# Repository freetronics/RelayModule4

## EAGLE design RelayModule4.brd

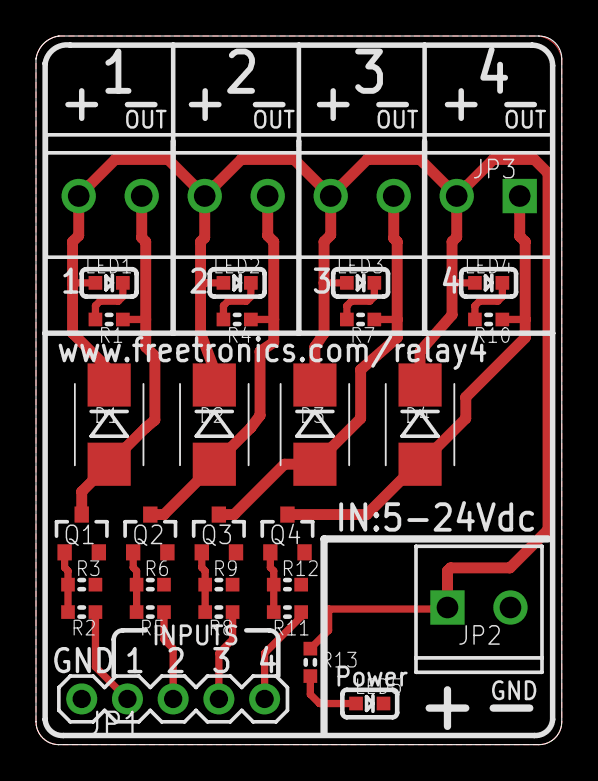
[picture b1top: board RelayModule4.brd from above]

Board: 2 copper layers, 29.2 x 39.4 mm, 30 parts (1 on the bottom side), 19 nets.

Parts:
D1, D2, D3, D4: 1N4004 SMB; SMB-DIODE
JP1: Power; 1X05
JP2: SCREWTERMINAL-3.5MM-2
JP3: TERMINALBLOCK_3.5MM_8
LED1: CH1/RED; LED-0603
LED2: CH2/RED; LED-0603
LED3: CH3/RED; LED-0603
LED4: CH4/RED; LED-0603
LED5: PWR/GRN; LED-0603
Q1, Q2, Q3, Q4: 2N7002; SOT23-3
R1, R2, R4, R5, R7, R8, R10, R11: 1K; 0603
R3, R6, R9, R12: 10K; 0603
R13: 2K2; 0603
U$5: OSHW_10X200_NOTEXT

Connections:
CH1: JP1.2, R2.2
CH2: JP1.3, R5.2
CH3: JP1.4, R8.2
CH4: JP1.5, R11.2
GND: JP1.1, JP2.2, LED5.C, Q1.2, Q2.2, Q3.2, Q4.2, R3.1, R6.1, R9.1, R12.1
unnamed: Q1.1, R2.1, R3.2
unnamed: D1.A, JP3.7, Q1.3, R1.2
unnamed: D2.A, JP3.5, Q2.3, R4.2
unnamed: LED5.A, R13.1
unnamed: Q2.1, R5.1, R6.2
unnamed: D3.A, JP3.3, Q3.3, R7.2
unnamed: Q3.1, R8.1, R9.2
unnamed: D4.A, JP3.1, Q4.3, R10.2
unnamed: Q4.1, R11.1, R12.2
unnamed: LED2.C, R4.1
unnamed: LED4.C, R10.1
unnamed: LED3.C, R7.1
unnamed: LED1.C, R1.1
V+: D1.C, D2.C, D3.C, D4.C, JP2.1, JP3.2, JP3.4, JP3.6, JP3.8, LED1.A, LED2.A, LED3.A, LED4.A, R13.2

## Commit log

2012-02-14 Initial project import
2012-02-14 Shuffling stuff around
2012-02-14 Rearranging and routing
2012-02-28 Layout and schematic cleanups
2012-03-27 Added license files
2012-03-27 Improved designator layout
2012-04-28 Start of experimental rework with 5mm screw terminal
2012-04-30 Updated routing and silkscreen
2012-05-06 sch layout and text, diodes, pcb overlay
2012-05-07 Tweak to designator locations
2019-04-24 Designators

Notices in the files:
RelayModule4.brd:
(c) 2012 Freetronics Pty Ltd
